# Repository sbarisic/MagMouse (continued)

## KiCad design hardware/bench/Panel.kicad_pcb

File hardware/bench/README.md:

# MagMouse Rev-A bench prototype

**Rev-A bench prototype — pending supplier/CAM approval. Do not order yet.**

Purchasing is limited to private-consumer suppliers; the user has no business.
CODICO business-only offers are excluded. Distinguish EU-stock items from
imports with Croatia shipping; see SOURCING.md for current evidence.

This variant targets five bare panels, one populated Main/Wheel/Encoder set,
and one unframed stencil. Main and Wheel remain the maintained routed source
boards. Encoder now shares their four-layer construction. U32 is omitted only
from the bench purchasing and paste variant; its schematic and footprint remain.

## Review files

- `MANUFACTURING_REVIEW.md`: completed local manufacturing review and JLC handoff.
- `package/CAM-review-attachments.zip`: consolidated, hashed CAM review attachments.
- `L1_REVIEW.md`: implemented Bourns replacement and local buck review.
- `HARNESS_REVIEW.md`: soldered-wire pin maps, lengths and pending optical identity.
- `STENCIL_REVIEW.md`: package dispositions and remaining process limits.
- `BENCH_ACCESS_REVIEW.md`: probe access, support and local copper findings.
- `supplier-drafts/`: unsent Ploopy/JLC CAM drafts and the superseded Würth follow-up;
  exported CAM draft identifies the actual ZIP hashes.

- `Panel.kicad_pro` / `Panel.kicad_pcb`: derived 151 x 139 mm, three-design panel.
- `panel-mechanical.svg`: printable outline and component-boundary review.
- `panel-manifest.json`: source hashes, board/reference mapping and translations.
- `package/Panel-Gerbers-QUOTE.zip`: copper, mask, silkscreen, routed edges and drills.
- `package/Stencil-QUOTE.zip`: top paste with U32 and hand-fitted parts excluded.
- `package/one-set-purchasing.csv`: exact MPN groups, references, quantities,
  minimum purchases, spares and public supplier observations.
- `package/all-vias.csv`: via-only fill/cap inventory. Never fill component holes,
  tooling holes or perforation holes.
- `BENCH_FIXTURE.md`, `bench-fixture.svg`: adjustable bench arrangement; no shell claim.
- `mechanical/bench/`: editable build123d, STEP/STL parts and dimensioned fixture views.
- `package/button-calibration.md`: fixed magnet endpoint calibration; runnable firmware is separate.
- `package/harness-pin-map.csv`: all 46 wires, component-side and mirrored solder-side views.
- `population-contract.json`: 282 retained parts, nine replaced connectors and U32 exclusion.
- `ASSEMBLY_AND_BRINGUP.md`: preparation, practice assembly and staged hardware tests.
- `SOURCING.md`, `WURTH_ENQUIRY.md`: supplier evidence and unresolved interfaces.
- `ORDER_READINESS.md`: remaining PCB work for a testable bench revision.
- `COST_CHECKPOINT.md`, `quote-observations.json`: live bare-board comparisons
  and the incomplete one-population cost estimate.
- `package/evidence/acceptance.json`: fresh native and strict electrical checks.
- `package/copper-review/`: exported copper and reference-plane views.

## Construction for both quotes

Order quantity five panels, **three different designs per panel**. Use FR4 TG155,
nominal 1.6 mm, four layers **JLC041611-2116**, 1 oz outer and 1 oz inner copper,
green mask, white silkscreen, ENIG 1 microinch and epoxy-filled/copper-capped vias.
The smallest vias are 0.20 mm drill / 0.45 mm pad; retain the source drill sizes.
The website's drill selection bucket does not authorize enlarging these holes.
Require CAM confirmation of the drill and fill specification.

The guaranteed variant requests 90 ohm differential USB, tolerance +/-10%.
The economy variant omits paid impedance control/testing only. Both retain
F.Cu width 0.1466 mm, gap 0.1501 mm and In1 ground reference. Do not accept a
stack substitution without a fresh impedance and return-path review.

All functional copper belongs to an individual board. No electrical connection
crosses a tab. The panel uses 2 mm separation clearance, ten 5 mm tabs with
five 0.6 mm perforations each, 0.9 mm pitch and 0.3 mm webs. Cut while supported
and **before population**. Do not bend populated boards to depanel them.

Selected Rev-A stencil: one 220 x 200 mm unframed stainless sheet, 0.10 mm thick,
three identifiable TOP aperture groups. Apply `paste_variant.py` for the
reviewed Hall/WSON/ADC apertures; copper and coordinates remain 1:1. JLC's multi-board option requires
permission to rearrange groups: approve the final CAM group positions before
building the alignment jig. A reordered stencil requires a regenerated jig.

## Reproduce and verify

Run with KiCad 10.0.6 Python, Shapely 2.1.2 and NumPy 2.4.6. The builder searches
`build/bench-python` for the latter libraries; dependencies are not vendored.

```powershell
& '<KiCad>/bin/python.exe' hardware/bench/build_panel.py
& '<KiCad>/bin/python.exe' hardware/bench/verify_bench.py
& '<KiCad>/bin/python.exe' hardware/bench/export_bench.py
& '<KiCad>/bin/python.exe' -m unittest discover -s hardware/bench -p 'test_*.py'
```

Two native panel builds were byte-identical. Export ZIP hashes change with KiCad
timestamps; the package hashes identify each exported snapshot. Copper/pad/via
and saved ground-fill transforms are checked against the individual source
boards. Source modification requires rebuilding and rerunning checks.

## Manufacturing and assembly items still open

The L1 replacement and soldered-wire migration are implemented; see ORDER_READINESS.md.
Ploopy is the user's selected optical supplier; exact lens/part confirmation
remains open. Wire/fixture fit, optical mounting and final ergonomic shell
development are assembly/mechanical tasks, not bench bare-board ordering gates.

1. Exact wire product, insulation/strand fit, continuity and strain-relief checks.
   The FFC enquiry requirement is superseded; no follow-up is sent.
2. Complete delivered parts/harness/mechanism/consumables pricing. Catalogue
   stock is not a reserved order; missing lines are not zero-cost parts.
3. Received lens/motor dimensions and practical bench fixture fit. Final shell,
   paddle geometry, optical retention and ergonomic wheel support remain open.
4. The 0.10 mm stencil design is selected; see STENCIL_REVIEW.md for accepted
   aperture geometry and volume tradeoffs. CAM confirms manufacturability.
   Paste/profile setup, practice reflow and hidden-joint inspection are assembly
   tasks, not bare-board ordering gates.
5. Fabricator acceptance of tab support, routability, minimum vias and selective
   fill/cap instructions. Zero native DRC is not manufacturing approval.
6. Complete delivered project total. The identical-stack separate-board
   comparison is complete and favors the panel. Never treat a partial subtotal
   as the €400 target.

CAD connectivity, DRC and regression results do not establish USB operation,
motor/brake behavior, analog noise, thermal performance or assembly yield.

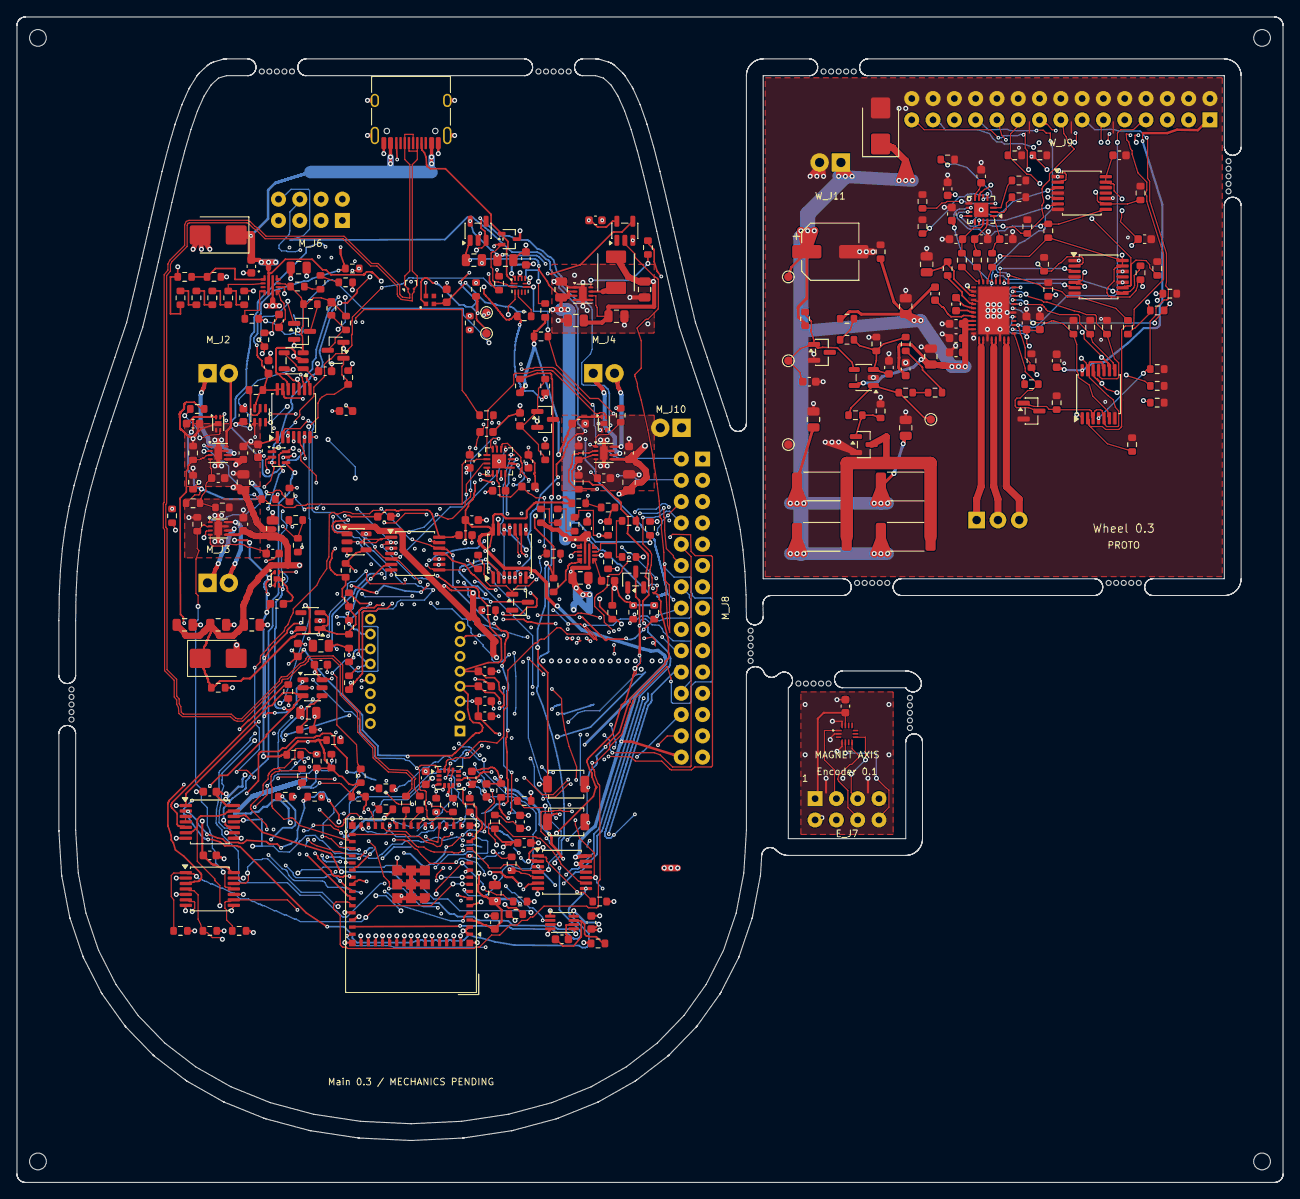
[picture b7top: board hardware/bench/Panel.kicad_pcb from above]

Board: 4 copper layers, 151.0 x 139.0 mm, 390 parts (37 on the bottom side), 193 nets.

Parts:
E_C62: 1uF/50V; C_0603_1608Metric
E_J7: Soldered wires Signal_2x04; Wire_Signal_2x04_P2.54mm
E_U27: MA735GGU-P; MPS_UTQFN14_2x2
MB1_1, MB1_2, MB1_3, MB1_4, MB1_5, MB2_1, MB2_2, MB2_3, MB2_4, MB2_5, MB3_1, MB3_2, MB3_3, MB3_4, MB3_5, MB4_1, MB4_2, MB4_3, MB4_4, MB4_5, MB5_1, MB5_2, MB5_3, MB5_4, MB5_5, MB6_1, MB6_2, MB6_3, MB6_4, MB6_5, MB7_1, MB7_2, MB7_3, MB7_4, MB7_5, MB8_1, MB8_2, MB8_3, MB8_4, MB8_5, MB9_1, MB9_2, MB9_3, MB9_4, MB9_5, MB10_1, MB10_2, MB10_3, MB10_4, MB10_5: NPTH
M_C1, M_C2, M_C3, M_C5, M_C8, M_C11, M_C14, M_C23, M_C37, M_C38, M_C39, M_C40, M_C73, M_C74, M_C77, M_C78, M_C88: 10uF/25V; C_0805_2012Metric
M_C4, M_C19, M_C20, M_C21, M_C24, M_C27, M_C63, M_C89: 1uF/50V; C_0603_1608Metric
M_C6, M_C7, M_C9, M_C10, M_C12, M_C13, M_C15, M_C16, M_C17, M_C18, M_C22, M_C28, M_C29, M_C30, M_C31, M_C32, M_C33, M_C34, M_C35, M_C36, M_C53, M_C55, M_C64, M_C70, M_C75, M_C76, M_C80, M_C83, M_C85, M_C86, M_C87: 100nF; C_0603_1608Metric
M_C25, M_C26, M_C72: 10nF; C_0603_1608Metric
M_C71, M_C81, M_C82: 2.2uF/10V; C_0603_1608Metric
M_C79: 1nF/50V; C_0603_1608Metric
M_C84: 4.7uF/10V; C_0603_1608Metric
M_D1: SMBJ12A; D_SMB
M_D2: SMBJ6.0A; D_SMB
M_D3, M_D4: BAT54-7-F; SOT-23
M_D5: SK6805-EC15; OPSCO_SK6805_EC15
M_J1: TYPE-C-31-M-12; USB_C_Receptacle_HRO_TYPE-C-31-M-12
M_J2, M_J3, M_J4, M_J10: Soldered wires Power_1x02; Wire_Power_1x02_P2.54mm
M_J6: Soldered wires Signal_2x04; Wire_Signal_2x04_P2.54mm
M_J8: Soldered wires Signal_2x15; Wire_Signal_2x15_P2.54mm
M_L1: SRP4020CC-3R3M; L_Bourns_SRP4020CC
M_Q1, M_Q2, M_Q3: 2N7002; SOT-23
M_R3, M_R4, M_R7, M_R8, M_R9, M_R10, M_R11, M_R14, M_R15, M_R16, M_R17, M_R20, M_R21, M_R22, M_R23, M_R30, M_R46, M_R47, M_R48, M_R49, M_R50, M_R51, M_R52, M_R53, M_R54, M_R55, M_R61, M_R70, M_R72, M_R73, M_R74, M_R75, M_R76, M_R77, M_R78, M_R79, M_R80, M_R99, M_R126, M_R127, M_R130, M_R131, M_R135: 10k; R_0603_1608Metric
M_R5, M_R6, M_R58: 33R; R_0603_1608Metric
M_R12, M_R18, M_R24, M_R42, M_R43, M_R56, M_R57, M_R60: 3.3k; R_0603_1608Metric
M_R25: 887k; R_0603_1608Metric
M_R26, M_R27, M_R31, M_R32, M_R33, M_R34, M_R35, M_R36, M_R37, M_R38, M_R39, M_R40, M_R62, M_R63, M_R66, M_R67, M_R71, M_R101, M_R110, M_R129, M_R133, M_R134, M_R136: 100k; R_0603_1608Metric
M_R28, M_R44, M_R45, M_R64, M_R69: 1k; R_0603_1608Metric
M_R29, M_R41, M_R65, M_R68: 22.1k; R_0603_1608Metric
M_R59: 4.7k; R_0603_1608Metric
M_R125: 0R; R_0603_1608Metric
M_R128: 330R; R_0603_1608Metric
M_R132: 39R; R_0603_1608Metric
M_R141, M_R142, M_R143: 33k; R_0603_1608Metric
M_SW1: RESET; SW_SPST_TS-1088-xR020
M_SW2: BOOT; SW_SPST_TS-1088-xR020
M_TP1, M_TP10: VBUS_USB; TestPoint_Pad_D1.0mm
M_TP2, M_TP11: PWR_5V; TestPoint_Pad_D1.0mm
M_TP3, M_TP12: ACT_5V; TestPoint_Pad_D1.0mm
M_TP4: UART_TX; TestPoint_Pad_D1.0mm
M_TP5: UART_RX; TestPoint_Pad_D1.0mm
M_TP6: MCU_EN; TestPoint_Pad_D1.0mm
M_TP7: BOOT; TestPoint_Pad_D1.0mm
M_TP8: +3V3; TestPoint_Pad_D1.0mm
M_TP9, M_TP15: GND; TestPoint_Pad_D1.0mm
M_TP13: ACT_DRIVE_EN; TestPoint_Pad_D1.0mm
M_TP14: USB_ILM; TestPoint_Pad_D1.0mm
M_TP16: CS_PAW; TestPoint_Pad_D1.0mm
M_TP17: WHEEL_RUN_REQ; TestPoint_Pad_D1.0mm
M_TP18: CS_IMU; TestPoint_Pad_D1.0mm
M_TP19: OPT_CTRL; TestPoint_Pad_D1.0mm
M_TP20: MOTOR_SPI_MOSI; TestPoint_Pad_D1.0mm
M_TP21: MOTOR_SPI_SCLK; TestPoint_Pad_D1.0mm
M_TP22: MOTOR_SPI_MISO; TestPoint_Pad_D1.0mm
M_TP23: CS_ADC2; TestPoint_Pad_D1.0mm
M_TP24: CS_MA735; TestPoint_Pad_D1.0mm
M_TP25: CS_DRV8316; TestPoint_Pad_D1.0mm
M_TP26: PAW_MOTION_N; TestPoint_Pad_D1.0mm
M_TP27: IMU_INT1; TestPoint_Pad_D1.0mm
M_TP28: DRV_FAULT_N; TestPoint_Pad_D1.0mm
M_TP29: WHEEL_PWM_A; TestPoint_Pad_D1.0mm
M_TP30: RGB_DATA; TestPoint_Pad_D1.0mm
M_TP31: BOOT_SAFE_SPARE; TestPoint_Pad_D1.0mm
M_TP32: WHEEL_PWM_B; TestPoint_Pad_D1.0mm
M_TP33: WHEEL_PWM_C; TestPoint_Pad_D1.0mm
M_TP38: RGB_5V; TestPoint_Pad_D1.0mm
M_TP39: RGB_DIN; TestPoint_Pad_D1.0mm
M_TP40: OPT_3V3; TestPoint_Pad_D1.0mm
M_TP41: OPT_1V9; TestPoint_Pad_D1.0mm
M_TP42: OPT_VDDPIX; TestPoint_Pad_D1.0mm
M_TP43: OPT_RESET_N; TestPoint_Pad_D1.0mm
M_U1: TPD2EUSB30DRTR; Texas_DRT-3
M_U2: TPS62162DSGR; Texas_DSG0008A_WSON-8-1EP_2x2mm_P0.5mm_EP0.9x1.6mm
M_U3: ESP32-S3-MINI-1-N8; ESP32-S2-MINI-1
M_U4, M_U5, M_U6: DRV8231ADSGR; Texas_DSG0008A_WSON-8-1EP_2x2mm_P0.5mm_EP0.9x1.6mm
M_U7, M_U8, M_U9: TMAG5253BA2IQDMRR; Texas_X2SON-4-1EP_1.1x1.4mm_P0.5mm_EP0.8x0.6mm
M_U10: ADS7038IRTER; WQFN-16-1EP_3x3mm_P0.5mm_EP1.68x1.68mm
M_U11: TUSB320LAIRWBR; Texas_X2QFN-12_1.6x1.6mm_P0.4mm
M_U12, M_U13: TPS259470LRPWR; Texas_RPW0010A
M_U14: SN74LVC2G04DCKR; SOT-363_SC-70-6
M_U15: SN74LVC1G123DCUR; VSSOP-8_2.3x2mm_P0.5mm
M_U16, M_U17, M_U18: SN74LVC08APWR; TSSOP-14_4.4x5mm_P0.65mm
M_U19: TLV9001IDBVR; SOT-23-5
M_U20: TPD2E2U06DCKR; SOT-323_SC-70
M_U25, M_U29, M_U37: SN74LVC125APWR; TSSOP-14_4.4x5mm_P0.65mm
M_U28: TPS22919DCKR; SOT-363_SC-70-6
M_U32: ICM-42688-P; LGA-14_3x2.5mm_P0.5mm_LayoutBorder3x4y
M_U33: TPS7A2450DBVR; SOT-23-5
M_U34: SN74LV1T34DBVR; SOT-23-5
M_U35: PMW3360DM-T2QU; PixArt_PMW3360DM_T2QU
M_U36: TLV75519PDBVR; SOT-23-5
M_U38: TPS22918DBVR; SOT-23-6
M_U39: SN74LVC1G125DBVR; SOT-23-5
TOOL1, TOOL2, TOOL3, TOOL4: NPTH
W_C41, W_C42, W_C43, W_C49, W_C51, W_C52, W_C54, W_C65, W_C66: 100nF; C_0603_1608Metric
W_C44, W_C45, W_C68, W_C69: 10uF/25V; C_0805_2012Metric
W_C46, W_C48, W_C56, W_C57, W_C58: 1uF/50V; C_0603_1608Metric
W_C47: 47nF/50V; C_0603_1608Metric
W_C50: 22uF/25V; C_0805_2012Metric
W_C59, W_C60, W_C61, W_C67: 22pF/50V; C_0603_1608Metric
W_C90: 100uF/16V; CP_Elec_6.3x5.9
W_D6: SMBJ6.0A; D_SMB
W_J5: GB1806 phase wires; MotorWire_3x1mm_P2.54mm
W_J9: Soldered wires Signal_2x15; Wire_Signal_2x15_P2.54mm
W_J11: Soldered wires Power_1x02; Wire_Power_1x02_P2.54mm
W_Q4: 2N7002; SOT-23
W_Q5: AO3400A; SOT-23
W_R81: 22R; R_0603_1608Metric
W_R82, W_R84, W_R86, W_R98, W_R111, W_R137, W_R138, W_R139, W_R140: 10k; R_0603_1608Metric
W_R83, W_R89, W_R90, W_R91, W_R92, W_R94, W_R95, W_R96, W_R97, W_R100, W_R112, W_R114, W_R120: 100k; R_0603_1608Metric
W_R87, W_R88, W_R146: 4.7k; R_0603_1608Metric
W_R102, W_R103, W_R104: 330R; R_0603_1608Metric
W_R105, W_R106, W_R107, W_R108, W_R109: 0R; R_0603_1608Metric
W_R113: 34.8k; R_0603_1608Metric
W_R115, W_R116, W_R117: 1M; R_0603_1608Metric
W_R119: 100R; R_0603_1608Metric
W_R121, W_R122, W_R123, W_R124: 47R/2W; R_2512_6332Metric
W_R144, W_R145: 33k; R_0603_1608Metric
W_TP34: ACT_5V; TestPoint_Pad_D1.0mm
W_TP35: BRAKE_REF; TestPoint_Pad_D1.0mm
W_TP36: BRAKE_OUT; TestPoint_Pad_D1.0mm
W_TP37: GND; TestPoint_Pad_D1.0mm
W_U21: DRV8316RRGFR; Texas_RGF0040E
W_U22: SN74LVC08APWR; TSSOP-14_4.4x5mm_P0.65mm
W_U23: ADS7038IRTER; WQFN-16-1EP_3x3mm_P0.5mm_EP1.68x1.68mm
W_U24, W_U26: SN74LVC125APWR; TSSOP-14_4.4x5mm_P0.65mm
W_U30: TLV1811DBVR; SOT-23-5
W_U31: LM4040AIM3-2.5/NOPB; SOT-23

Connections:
Encoder/ENC_3V3: E_C62.1, E_J7.1, E_U27.13
Encoder/ENC_CS_LOCAL: E_J7.6, E_U27.7
Encoder/ENC_MISO_LOCAL: E_J7.8, E_U27.5
Encoder/ENC_MOSI_LOCAL: E_J7.5, E_U27.8
Encoder/ENC_SCLK_LOCAL: E_J7.3, E_U27.1
Encoder/GND: E_C62.2, E_J7.2, E_J7.4, E_J7.7, E_U27.2, E_U27.4, E_U27.14
Main/+3V3: M_C2.1, M_C3.1, M_C5.1, M_C6.1, M_C16.1, M_C17.1, M_C18.1, M_C19.1, M_C20.1, M_C22.1, M_C23.1, M_C28.1, M_C29.1, M_C30.1, M_C31.1, M_C32.1, M_C34.1, M_C53.1, M_C63.1, M_C70.1, M_C71.1, M_C72.1, M_C77.1, M_C78.1, M_D4.3, M_J8.30, M_L1.2, M_R3.1, M_R4.1, M_R7.1, M_R10.1, M_R16.1, M_R22.1, M_R26.1, M_R27.1, M_R46.1, M_R71.1, M_R72.1, M_R73.1, M_R74.1, M_R75.1, M_R76.1, M_R127.1, M_TP8.1, M_U2.6, M_U3.3, M_U7.1, M_U8.1, M_U9.1, M_U10.7, M_U10.10, M_U11.12, M_U14.5, M_U15.8, M_U16.14, M_U17.14, M_U18.14, M_U19.5, M_U25.14, M_U28.1, M_U32.5, M_U32.8, M_U38.1
Main/ACT_5V: M_C7.1, M_C8.1, M_C10.1, M_C11.1, M_C13.1, M_C14.1, M_C37.1, M_C38.1, M_C39.1, M_C40.1, M_D2.1, M_J10.1, M_R67.1, M_R69.1, M_TP3.1, M_TP12.1, M_U4.5, M_U5.5, M_U6.5, M_U13.6
Main/ACT_DRIVE_EN: M_D3.3, M_J8.24, M_R49.1, M_TP13.1, M_U16.11, M_U17.2, M_U17.5, M_U17.10, M_U17.13, M_U18.2, M_U18.5
Main/ACT_DVDT: M_C26.1, M_U13.7
Main/ACT_FAULT_N: M_R45.1, M_U13.4
Main/ACT_HEARTBEAT: M_R47.1, M_U3.21, M_U15.2
Main/ACT_ILM: M_R42.1, M_R43.1, M_U13.9
Main/ACT_OVLO: M_R40.2, M_R41.1, M_U13.2
Main/ACT_PERMIT: M_U15.5, M_U16.12
Main/ACT_REQ: M_R48.1, M_U3.20, M_U16.2
Main/ACT_UVLO: M_D3.1, M_R38.2, M_R39.1, M_U13.1
Main/ACT_UV_1: M_R36.2, M_R37.1
Main/ACT_UV_2: M_R37.2, M_R38.1
Main/ACT_VMON: M_C36.1, M_D4.1, M_R67.2, M_R68.1, M_U10.6
Main/ADC2_MISO_LOCAL: M_J8.16, M_R143.1, M_U25.9
Main/ADC_CS: M_R7.2, M_U3.14, M_U10.11
Main/ADC_DECAP: M_C21.1, M_U10.8
Main/ARM_SOURCE: M_U16.3, M_U16.4
Main/ARM_VALID: M_U15.3, M_U16.6, M_U16.13
Main/BOOT: M_R4.2, M_SW2.1, M_TP7.1, M_U3.4
Main/BOOT_SAFE_SPARE: M_R80.1, M_TP31.1, M_U3.44
Main/BTN_L_CMD1: M_R50.1, M_U3.8, M_U17.1
Main/BTN_L_CMD2: M_R51.1, M_U3.9, M_U17.4
Main/BTN_L_COIL_N: M_J2.2, M_U4.8
Main/BTN_L_COIL_P: M_J2.1, M_U4.6
Main/BTN_L_IN1: M_R8.1, M_U4.3, M_U17.3
Main/BTN_L_IN2: M_R9.1, M_U4.2, M_U17.6
Main/BTN_L_ISENSE: M_R12.1, M_U4.1, M_U10.2
Main/BTN_L_VREF: M_C9.1, M_R10.2, M_R11.1, M_U4.4
Main/BTN_M_CMD1: M_R52.1, M_U3.10, M_U17.9
Main/BTN_M_CMD2: M_R53.1, M_U3.11, M_U17.12
Main/BTN_M_COIL_N: M_J3.2, M_U5.8
Main/BTN_M_COIL_P: M_J3.1, M_U5.6
Main/BTN_M_IN1: M_R14.1, M_U5.3, M_U17.8
Main/BTN_M_IN2: M_R15.1, M_U5.2, M_U17.11
Main/BTN_M_ISENSE: M_R18.1, M_U5.1, M_U10.3
Main/BTN_M_VREF: M_C12.1, M_R16.2, M_R17.1, M_U5.4
Main/BTN_R_CMD1: M_R54.1, M_U3.12, M_U18.1
Main/BTN_R_CMD2: M_R55.1, M_U3.13, M_U18.4
Main/BTN_R_COIL_N: M_J4.2, M_U6.8
Main/BTN_R_COIL_P: M_J4.1, M_U6.6
Main/BTN_R_IN1: M_R20.1, M_U6.3, M_U18.3
Main/BTN_R_IN2: M_R21.1, M_U6.2, M_U18.6
Main/BTN_R_ISENSE: M_R24.1, M_U6.1, M_U10.4
Main/BTN_R_VREF: M_C15.1, M_R22.2, M_R23.1, M_U6.4
Main/BUCK_SW: M_L1.1, M_U2.7
Main/CC_OUT1: M_R26.2, M_U3.18, M_U11.7, M_U14.1
Main/CC_OUT2: M_R27.2, M_U3.19, M_U11.8, M_U14.3
Main/CC_OUT2_INV: M_U14.4, M_U16.10
Main/CC_VBUS_DET: M_R25.2, M_U11.4
Main/CS_ADC2: M_J8.14, M_R74.2, M_TP23.1, M_U3.32, M_U25.10
Main/CS_DRV8316: M_J8.6, M_R76.2, M_TP25.1, M_U3.34, M_U25.1
Main/CS_IMU: M_R73.2, M_TP18.1, M_U3.25, M_U32.12
Main/CS_MA735: M_R75.2, M_TP24.1, M_U3.33, M_U25.4, M_U29.9
Main/CS_PAW: M_R72.2, M_TP16.1, M_U3.6, M_U37.1, M_U37.4, M_U37.10, M_U39.2
Main/DRV_FAULT_LOCAL_N: M_J8.28, M_R141.1, M_U25.12
Main/DRV_FAULT_N: M_TP28.1, M_U3.37, M_U25.11
Main/DRV_MISO_LOCAL: M_J8.8, M_R142.1, M_U25.2
Main/ENC_3V3: M_C55.1, M_C64.1, M_J6.1, M_R99.1, M_R125.2, M_U28.6, M_U29.13, M_U29.14
Main/ENC_CS_LOCAL: M_J6.6, M_R99.2, M_U29.8
Main/ENC_MISO_LOCAL: M_J6.8, M_R101.1, M_U25.5
Main/ENC_MOSI_LOCAL: M_J6.5, M_U29.6
Main/ENC_QOD: M_R125.1, M_U28.5
Main/ENC_SCLK_LOCAL: M_J6.3, M_U29.3
Main/GND: M_C1.2, M_C2.2, M_C3.2, M_C4.2, M_C5.2, M_C6.2, M_C7.2, M_C8.2, M_C9.2, M_C10.2, M_C11.2, M_C12.2, M_C13.2, M_C14.2, M_C15.2, M_C16.2, M_C17.2, M_C18.2, M_C19.2, M_C20.2, M_C21.2, M_C22.2, M_C23.2, M_C24.2, M_C25.2, M_C26.2, M_C28.2, M_C29.2, M_C30.2, M_C31.2, M_C32.2, M_C33.2, M_C34.2, M_C35.2, M_C36.2, M_C37.2, M_C38.2, M_C39.2, M_C40.2, M_C53.2, M_C55.2, M_C63.2, M_C64.2, M_C70.2, M_C71.2, M_C72.2, M_C73.2, M_C74.2, M_C75.2, M_C76.2, M_C77.2, M_C78.2, M_C79.2, M_C80.2, M_C81.2, M_C82.2, M_C83.2, M_C84.2, M_C85.2, M_C86.2, M_C87.2, M_C88.2, M_C89.2, M_D1.2, M_D2.2, M_D5.4, M_J1.A1, M_J1.A12, M_J1.B1, M_J1.B12, M_J1.SH, M_J6.2, M_J6.4, M_J6.7, M_J8.1, M_J8.3, M_J8.5, M_J8.7, M_J8.9, M_J8.11, M_J8.13, M_J8.15, M_J8.17, M_J8.19, M_J8.21, M_J8.23, M_J8.25, M_J8.27, M_J8.29, M_J10.2, M_Q1.2, M_Q2.2, M_Q3.2, M_R8.2, M_R9.2, M_R11.2, M_R12.2, M_R14.2, M_R15.2, M_R17.2, M_R18.2, M_R20.2, M_R21.2, M_R23.2, M_R24.2, M_R30.2, M_R35.2, M_R39.2, M_R41.2, M_R42.2, M_R43.2, M_R47.2, M_R48.2, M_R49.2, M_R50.2, M_R51.2, M_R52.2, M_R53.2, M_R54.2, M_R55.2, M_R58.2, M_R62.2, M_R63.2, M_R66.2, M_R68.2, M_R69.2, M_R70.2, M_R77.2, M_R78.2, M_R79.2, M_R80.2, M_R101.2, M_R110.2, M_R126.2, M_R129.2, M_R130.2, M_R134.2, M_R141.2, M_R142.2, M_R143.2, M_SW1.2, M_SW2.2, M_TP9.1, M_TP15.1, M_U1.3, M_U2.1, M_U2.4, M_U2.5, M_U2.9, M_U3.1, M_U3.2, M_U3.42, M_U3.43, M_U3.46, M_U3.47, M_U3.48, M_U3.49, M_U3.50, M_U3.51, M_U3.52, M_U3.53, M_U3.54, M_U3.55, M_U3.56, M_U3.57, M_U3.58, M_U3.59, M_U3.60, M_U3.61, M_U3.62, M_U3.63, M_U3.64, M_U3.65, M_U4.7, M_U4.9, M_U5.7, M_U5.9, M_U6.7, M_U6.9, M_U7.2, M_U7.5, M_U8.2, M_U8.5, M_U9.2, M_U9.5, M_U10.9, M_U10.17, M_U11.3, M_U11.10, M_U11.11, M_U12.8, M_U13.8, M_U14.2, M_U15.1, M_U15.4, M_U16.7, M_U17.7, M_U18.7, M_U18.12, M_U18.13, M_U19.2, M_U20.3, M_U25.7, M_U25.13, M_U28.2, M_U29.1, M_U29.4, M_U29.7, M_U29.10, M_U29.12, M_U32.6, M_U32.7, M_U33.2, M_U34.3, M_U35.8, M_U36.2, M_U37.7, M_U37.13, M_U38.2, M_U39.1, M_U39.3
Main/HALL_EN: M_R110.1, M_U7.3, M_U8.3, M_U9.3, M_U16.5, M_U18.8, M_U28.3, M_U33.3, M_U38.3
Main/HALL_L: M_U7.4, M_U10.15
Main/HALL_M: M_U8.4, M_U10.16
Main/HALL_R: M_U9.4, M_U10.1
Main/ILM_BASE_1: M_R56.2, M_R57.1
Main/ILM_BASE_2: M_R57.2, M_R58.1
Main/ILM_HIGH_D: M_Q2.3, M_R60.2, M_R61.2
Main/ILM_MED_D: M_Q1.3, M_R59.2
Main/IMU_INT1: M_R127.2, M_TP27.1, M_U3.36, M_U32.4
Main/IMU_PIN9: M_R126.1, M_U32.9
Main/LOGIC_PG: M_R28.1, M_U2.8
Main/MCU_EN: M_C4.1, M_R3.2, M_R28.2, M_R44.2, M_R45.2, M_SW1.1, M_TP6.1, M_U3.45, M_U18.10
Main/MCU_USB_DM: M_R5.1, M_U3.23
Main/MCU_USB_DP: M_R6.1, M_U3.24
Main/MOTOR_SPI_MISO: M_TP22.1, M_U3.31, M_U25.8
Main/MOTOR_SPI_MOSI: M_J8.12, M_TP20.1, M_U3.28
Main/MOTOR_SPI_SCLK: M_J8.10, M_TP21.1, M_U3.29
Main/OPT_1V9: M_C82.1, M_C83.1, M_R132.1, M_TP41.1, M_U35.4, M_U36.5
Main/OPT_3V3: M_C80.1, M_C81.1, M_C86.1, M_C87.1, M_R131.1, M_R133.1, M_R135.1, M_R136.1, M_TP40.1, M_U35.5, M_U36.1, M_U36.3, M_U37.14, M_U38.6, M_U39.5
Main/OPT_CS_N: M_R131.2, M_U35.13, M_U39.4
Main/OPT_CTRL: M_R79.1, M_TP19.1, M_U3.26, M_U37.12
Main/OPT_LED_P: M_R132.2, M_U35.15
Main/OPT_MISO: M_R135.2, M_U35.12, M_U37.9
Main/OPT_MOSI: M_R134.1, M_U35.11, M_U37.3
Main/OPT_RAMP_CT: M_C79.1, M_U38.4
Main/OPT_RESET_N: M_TP43.1, M_U35.7, M_U37.11
Main/OPT_SCLK: M_R133.2, M_U35.10, M_U37.6
Main/OPT_VDDPIX: M_C84.1, M_C85.1, M_TP42.1, M_U35.3
Main/PAW_MOTION_N: M_R136.2, M_TP26.1, M_U3.35, M_U35.9
Main/PWR_5V: M_C1.1, M_C73.1, M_C88.1, M_C89.1, M_R36.1, M_R40.1, M_TP2.1, M_TP11.1, M_U2.2, M_U2.3, M_U12.6, M_U13.5, M_U33.1
Main/RGB_5V: M_C74.1, M_C75.1, M_C76.1, M_D5.2, M_R130.1, M_TP38.1, M_U33.5, M_U34.5
Main/RGB_BUFFER_OUT: M_R128.1, M_U34.4
Main/RGB_DATA: M_R78.1, M_TP30.1, M_U3.41, M_U34.2
Main/RGB_DIN: M_D5.1, M_R128.2, M_R129.1, M_TP39.1
Main/SENS_REQ: M_R70.1, M_U3.22, M_U18.9
Main/SOURCE_3A: M_Q2.1, M_R63.1, M_U16.8
Main/SOURCE_OK: M_Q1.1, M_R62.1, M_U14.6, M_U16.1, M_U16.9
Main/SPI_MISO: M_U3.17, M_U10.12, M_U25.3, M_U25.6, M_U32.1, M_U37.8
Main/SPI_MOSI: M_J8.4, M_U3.15, M_U10.14, M_U29.5, M_U32.14, M_U37.2
Main/SPI_SCLK: M_J8.2, M_U3.16, M_U10.13, M_U29.2, M_U32.13, M_U37.5
Main/UART_RX: M_TP5.1, M_U3.40
Main/UART_TX: M_TP4.1, M_U3.39
Main/USB_CC1: M_J1.A5, M_U11.1, M_U20.1
Main/USB_CC2: M_J1.B5, M_U11.2, M_U20.2
Main/USB_DM: M_J1.A7, M_J1.B7, M_R5.2, M_U1.2
Main/USB_DP: M_J1.A6, M_J1.B6, M_R6.2, M_U1.1
Main/USB_DVDT: M_C25.1, M_U12.7
Main/USB_FAULT_N: M_R44.1, M_U12.4
Main/USB_ILM: M_R56.1, M_R59.1, M_R60.1, M_R61.1, M_TP14.1, M_U12.9, M_U19.3
Main/USB_IMON_ADC: M_C33.1, M_R64.2, M_U10.5
Main/USB_IMON_BUF: M_R64.1, M_U19.1, M_U19.4
Main/USB_OVLO: M_R34.2, M_R35.1, M_U12.2
Main/USB_OV_1: M_R31.2, M_R32.1
Main/USB_OV_2: M_R32.2, M_R33.1
Main/USB_OV_3: M_R33.2, M_R34.1
Main/USB_UVLO: M_R29.2, M_R30.1, M_U12.1
Main/VBUS_GATE: M_C35.1, M_Q3.1, M_R65.2, M_R66.1
Main/VBUS_PRESENT_N: M_Q3.3, M_R71.2, M_U3.5
Main/VBUS_USB: M_C24.1, M_D1.1, M_J1.A4, M_J1.A9, M_J1.B4, M_J1.B9, M_R25.1, M_R29.1, M_R31.1, M_R65.1, M_TP1.1, M_TP10.1, M_U12.5
Main/WD_CEXT: M_C27.2, M_U15.6
Main/WD_RCEXT: M_C27.1, M_R46.2, M_U15.7
Main/WHEEL_PWM_A: M_J8.18, M_TP29.1, M_U3.38
Main/WHEEL_PWM_B: M_J8.20, M_TP32.1, M_U3.27
Main/WHEEL_PWM_C: M_J8.22, M_TP33.1, M_U3.30
Main/WHEEL_RUN_REQ: M_J8.26, M_R77.1, M_TP17.1, M_U3.7
Wheel/+3V3: W_C51.1, W_J9.1, W_U22.14
Wheel/ACT_5V: W_C41.1, W_C42.1, W_C43.1, W_C44.1, W_C45.1, W_C46.2, W_C65.1, W_C68.1, W_C69.1, W_C90.1, W_D6.1, W_J11.1, W_R111.1, W_R112.1, W_R121.1, W_R122.1, W_R123.1, W_R124.1, W_R146.1, W_TP34.1, W_U21.9, W_U21.10, W_U21.11, W_U30.5
Wheel/ACT_DRIVE_EN: W_J9.7, W_R84.1, W_U21.23, W_U22.1
Wheel/ADC2_CS_LOCAL: W_R98.2, W_U23.11, W_U26.8
Wheel/ADC2_DECAP: W_C58.1, W_U23.8
Wheel/ADC2_MISO_LOCAL: W_J9.15, W_R100.1, W_U23.12
Wheel/ADC2_MOSI_LOCAL: W_U23.14, W_U26.6
Wheel/ADC2_SCLK_LOCAL: W_U23.13, W_U26.3
Wheel/ADC2_SPARE3: W_R105.1, W_U23.2
Wheel/ADC2_SPARE4: W_R106.1, W_U23.3
Wheel/ADC2_SPARE5: W_R107.1, W_U23.4
Wheel/ADC2_SPARE6: W_R108.1, W_U23.5
Wheel/ADC2_SPARE7: W_R109.1, W_U23.6
Wheel/BRAKE_DIV_TOP: W_R112.2, W_R113.1
Wheel/BRAKE_DRAIN: W_Q5.3, W_R121.2, W_R122.2, W_R123.2, W_R124.2
Wheel/BRAKE_FB_1: W_R115.2, W_R116.1
Wheel/BRAKE_FB_2: W_R116.2, W_R117.1
Wheel/BRAKE_GATE: W_Q5.1, W_R119.2, W_R120.1
Wheel/BRAKE_OUT: W_R115.1, W_R119.1, W_TP36.1, W_U30.1
Wheel/BRAKE_REF: W_C66.1, W_R111.2, W_TP35.1, W_U30.4, W_U31.1
Wheel/BRAKE_SENSE: W_C67.1, W_R113.2, W_R114.1, W_R117.2, W_U30.3
Wheel/CS_ADC2: W_J9.17, W_R145.1, W_U26.9
Wheel/CS_DRV8316: W_J9.25, W_R144.1, W_U24.9
Wheel/DRV_AVDD: W_C48.1, W_C49.1, W_C52.1, W_C54.1, W_C56.1, W_C57.1, W_R82.1, W_R86.1, W_R87.1, W_R88.1, W_R98.1, W_U21.25, W_U21.37, W_U23.7, W_U23.10, W_U24.13, W_U24.14, W_U26.13, W_U26.14
Wheel/DRV_CS_LOCAL: W_R86.2, W_U21.36, W_U24.8
Wheel/DRV_FAULT_LOCAL_N: W_J9.3, W_R88.2, W_R89.1, W_U21.22
Wheel/DRV_INHA: W_R90.1, W_U21.27, W_U22.6
Wheel/DRV_INHB: W_R91.1, W_U21.29, W_U22.8
Wheel/DRV_INHC: W_R92.1, W_U21.31, W_U22.11
Wheel/DRV_MISO_LOCAL: W_J9.23, W_R87.2, W_U21.33
Wheel/DRV_MOSI_LOCAL: W_U21.34, W_U24.6
Wheel/DRV_SCLK_LOCAL: W_U21.35, W_U24.3
Wheel/GND: W_C41.2, W_C42.2, W_C43.2, W_C44.2, W_C45.2, W_C48.2, W_C49.2, W_C50.2, W_C51.2, W_C52.2, W_C54.2, W_C56.2, W_C57.2, W_C58.2, W_C59.2, W_C60.2, W_C61.2, W_C65.2, W_C66.2, W_C67.2, W_C68.2, W_C69.2, W_C90.2, W_D6.2, W_J9.2, W_J9.4, W_J9.6, W_J9.8, W_J9.10, W_J9.12, W_J9.14, W_J9.16, W_J9.18, W_J9.20, W_J9.22, W_J9.24, W_J9.26, W_J9.28, W_J9.30, W_J11.2, W_Q4.2, W_Q5.2, W_R83.2, W_R84.2, W_R89.2, W_R90.2, W_R91.2, W_R92.2, W_R94.2, W_R95.2, W_R96.2, W_R97.2, W_R100.2, W_R105.2, W_R106.2, W_R107.2, W_R108.2, W_R109.2, W_R114.2, W_R120.2, W_R137.2, W_R138.2, W_R139.2, W_R140.2, W_R144.2, W_R145.2, W_R146.2, W_TP37.1, W_U21.2, W_U21.4, W_U21.12, W_U21.15, W_U21.18, W_U21.26, W_U21.41, W_U22.7, W_U23.9, W_U23.17, W_U24.1, W_U24.4, W_U24.7, W_U24.10, W_U24.12, W_U26.1, W_U26.4, W_U26.7, W_U26.10, W_U26.12, W_U30.2, W_U31.2
Wheel/MOTOR_SPI_MOSI: W_J9.19, W_R97.1, W_U26.5
Wheel/MOTOR_SPI_SCLK: W_J9.21, W_R96.1, W_U26.2
Wheel/SPI_MOSI: W_J9.27, W_R95.1, W_U24.5
Wheel/SPI_SCLK: W_J9.29, W_R94.1, W_U24.2
Wheel/WHEEL_BUCK_OUT: W_C50.1, W_R81.2, W_U21.3
Wheel/WHEEL_BUCK_SW: W_R81.1, W_U21.5
Wheel/WHEEL_CP: W_C46.1, W_U21.8
Wheel/WHEEL_CPH: W_C47.1, W_U21.7
Wheel/WHEEL_CPL: W_C47.2, W_U21.6
Wheel/WHEEL_DRVOFF: W_Q4.3, W_R82.2, W_U21.21
Wheel/WHEEL_I_A: W_C59.1, W_R102.2, W_U23.15
Wheel/WHEEL_I_B: W_C60.1, W_R103.2, W_U23.16
Wheel/WHEEL_I_C: W_C61.1, W_R104.2, W_U23.1
Wheel/WHEEL_PHASE_A: W_J5.1, W_U21.13, W_U21.14
Wheel/WHEEL_PHASE_B: W_J5.2, W_U21.16, W_U21.17
Wheel/WHEEL_PHASE_C: W_J5.3, W_U21.19, W_U21.20
Wheel/WHEEL_PWM_A: W_J9.13, W_R138.1, W_U22.4
Wheel/WHEEL_PWM_B: W_J9.11, W_R139.1, W_U22.9
Wheel/WHEEL_PWM_C: W_J9.9, W_R140.1, W_U22.12
Wheel/WHEEL_RUN_EN: W_Q4.1, W_R83.1, W_U21.28, W_U21.30, W_U21.32, W_U22.3, W_U22.5, W_U22.10, W_U22.13
Wheel/WHEEL_RUN_REQ: W_J9.5, W_R137.1, W_U22.2
Wheel/WHEEL_SOA: W_R102.1, W_U21.40
Wheel/WHEEL_SOB: W_R103.1, W_U21.39
Wheel/WHEEL_SOC: W_R104.1, W_U21.38
